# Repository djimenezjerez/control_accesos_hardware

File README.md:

# Hardware para el sistema de control de accesos

## Requisitos

Para abrir los archivos necesita tener instalado el software [KiCad](http://kicad-pcb.org/), con lo que podrá ejecutar los archivos .pro (Project) dentro de los cuales se encuentra el esquemático de la placa de interfaz sensorial que también cumple la función de control central de puertas, y la placa de respaldo bluetooth para apertura de puertas en caso de emergencia.

Para continuar el desarrollo de la aplicación de Android es necesario importar el archivo del proyecto [MIT App Inventor 2](./control_puertas.aia) y generar el APK desde la propia aplicación.

Los componentes del sistema son:

* [Hardware registrador](https://github.com/djimenezjerez/control_accesos_registrador)
* [Backend de administración del sistema](https://github.com/djimenezjerez/control_accesos_backend)
* [Frontend de administración del sistema](https://github.com/djimenezjerez/control_accesos_frontend)

## Documentación

* [LPG-Bolivia](https://softwarelibre.gob.bo/licencia.php)

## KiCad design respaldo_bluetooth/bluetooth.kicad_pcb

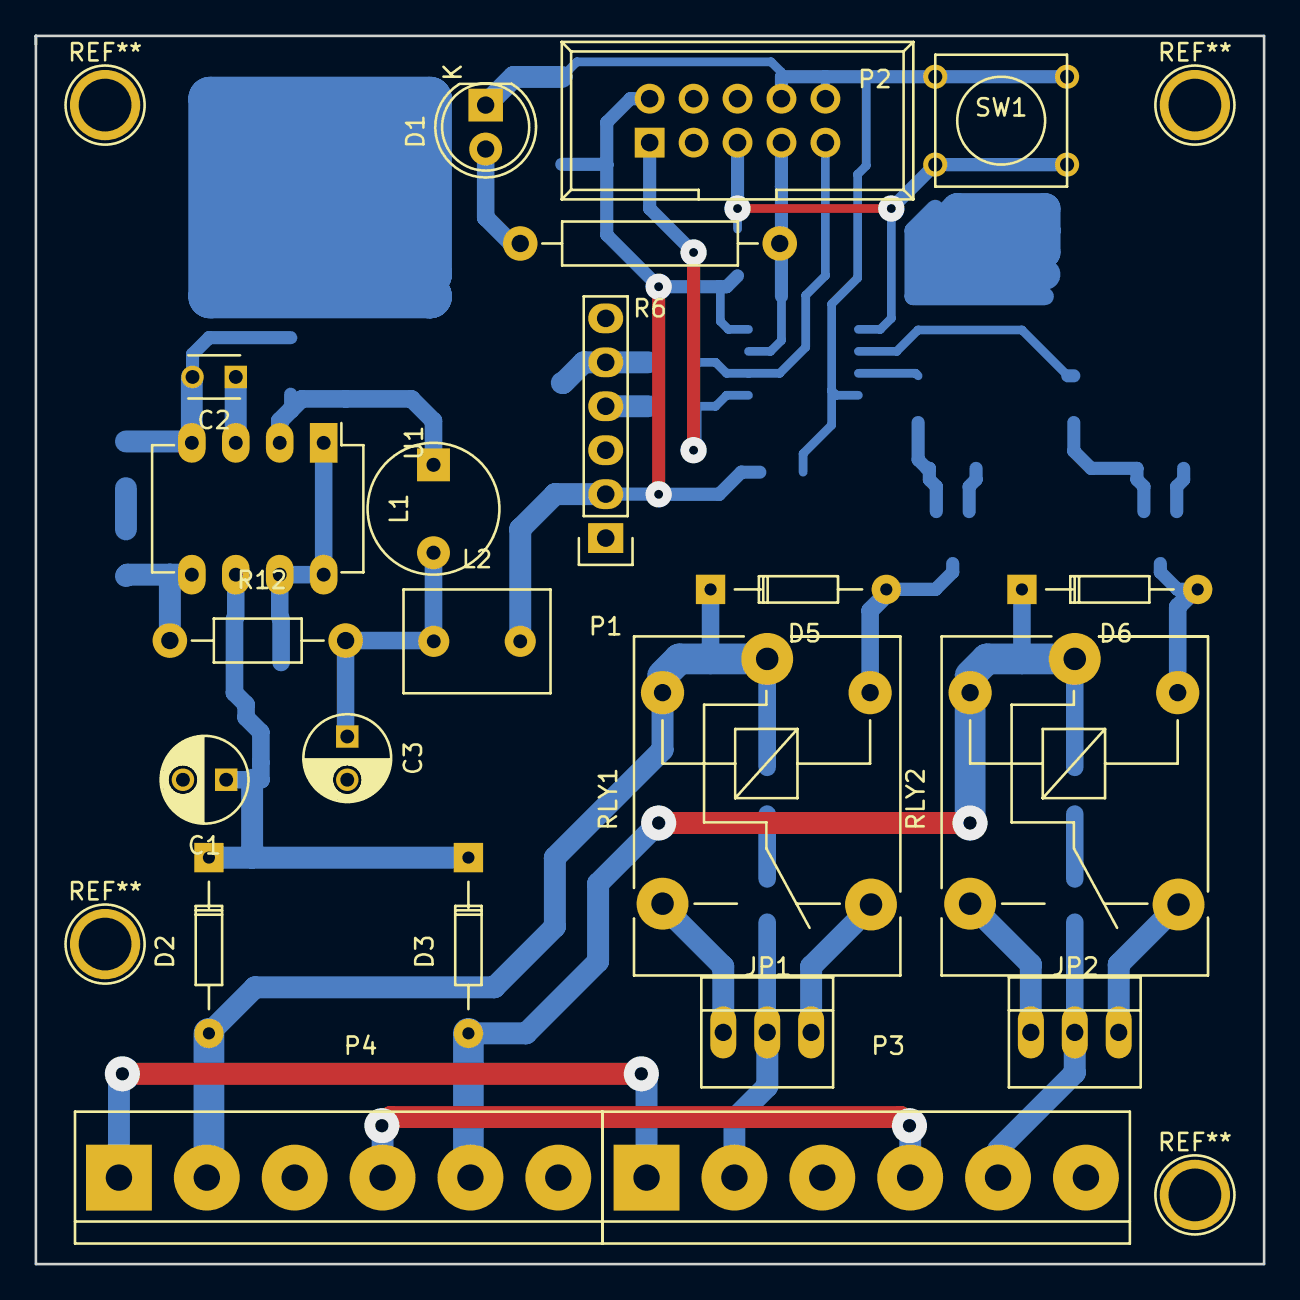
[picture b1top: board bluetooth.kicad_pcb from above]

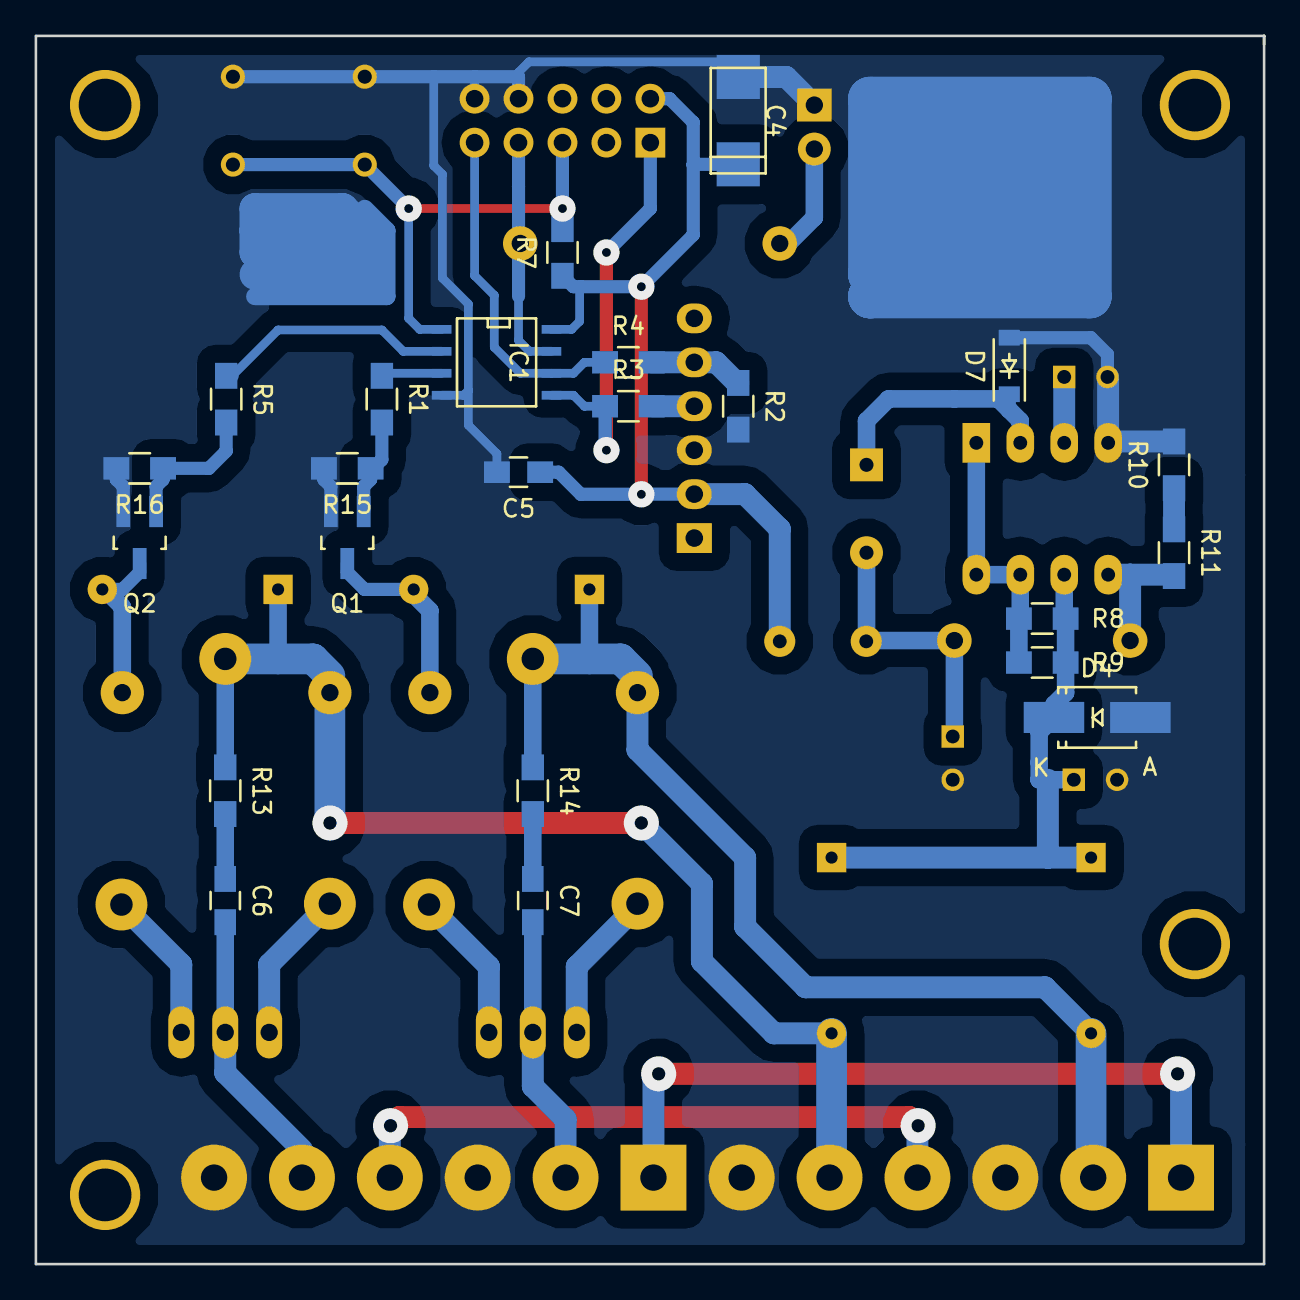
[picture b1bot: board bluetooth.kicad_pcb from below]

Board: 2 copper layers, 71.0 x 71.0 mm, 45 parts (23 on the bottom side), 34 nets.

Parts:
C1: 100uF; C_Radial_D5_L11_P2.5
C2: 470pF; C_Disc_D3_P2.5
C3: 47uF; C_Radial_D5_L11_P2.5
C4: 100uF; TantalC_SizeU_EIA-6032
C5, C6, C7: 100nF; C_0805_HandSoldering
D1: LED; LED-5MM
D2, D3: 1N4001; Diode_DO-35_SOD27_Horizontal_RM10
D4: TVS; SMA_Handsoldering
D5, D6: 1N4148; Diode_DO-35_SOD27_Horizontal_RM10
D7: 1N5819; SOD-123
IC1: ATTINY85-S; SOIC-8-N
JP1, JP2: NO/NC; PINHEAD1-3
L1: 150uH; INDUCTOR_V
L2: 150uH; Neosid_Inductor_MA-Bs75
P1: HC05-module; Pin_Header_Straight_1x06
P2: CONN_02X05; IDC_Header_Straight_10pins
P3: SALIDA; bornier6
P4: ENTRADA; bornier6
Q1, Q2: BCX70K; SOT-23_Handsoldering
R1, R2, R3, R4, R5, R7, R15, R16: R; R_0805_HandSoldering
R6: R; Resistor_Horizontal_RM15mm
R8, R9: 1R; R_0805_HandSoldering
R10: 1K; R_0805_HandSoldering
R11, R13, R14: 100R; R_0805_HandSoldering
R12: 3K3; Resistor_Horizontal_RM10mm
RLY1, RLY2: RELAY_HJR-3FF_Z; Relay_SANYOU_SRD_Series_Form_C
SW1: SW_PUSH; SW_PUSH_SMALL
U1: MC34063A; DIP-8_W7.62mm_LongPads

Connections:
+5V: C4.1, C5.1, IC1.8, L2.2, P1.2, P2.2, R7.1
GND: C1.2, C2.2, C3.2, C4.2, C5.2, D1.1, D4.2, D7.2, IC1.4, P1.3, P2.8, P2.10, P3.3, P3.6, P4.3, P4.6, Q1.2, Q2.2, R2.2, R10.2, R15.2, R16.2, SW1.1, U1.4
unnamed: C1.1, D2.1, D3.1, D4.1, R8.2, R9.2, U1.6
unnamed: C2.1, U1.3
unnamed: C3.1, L1.2, L2.1, R12.2
unnamed: C6.1, R13.2
unnamed: C6.2, JP2.2, P3.5
unnamed: C7.1, R14.2
unnamed: C7.2, JP1.2, P3.2
unnamed: D1.2, R6.2
unnamed: D2.2, D5.1, P4.2, R14.1, RLY1.1, RLY1.2
unnamed: D3.2, D6.1, P4.5, R13.1, RLY2.1, RLY2.2
unnamed: D5.2, Q1.3, RLY1.5
unnamed: D6.2, Q2.3, RLY2.5
unnamed: D7.1, L1.1, U1.2
unnamed: IC1.1, P2.5, R7.2, SW1.2
unnamed: IC1.2, R5.1
unnamed: IC1.3, R1.1
unnamed: IC1.5, P2.1, R3.1
unnamed: IC1.6, P2.9, R4.1
unnamed: IC1.7, P2.7, R6.1
unnamed: JP1.1, RLY1.3
unnamed: JP1.3, RLY1.4
unnamed: JP2.1, RLY2.3
unnamed: JP2.3, RLY2.4
unnamed: P1.4, R3.2
unnamed: P1.5, R2.1, R4.2
unnamed: P3.1, P4.1
unnamed: P3.4, P4.4
unnamed: Q1.1, R1.2, R15.1
unnamed: Q2.1, R5.2, R16.1
unnamed: R8.1, R9.1, U1.1, U1.7, U1.8
unnamed: R10.1, R11.1
unnamed: R11.2, R12.1, U1.5

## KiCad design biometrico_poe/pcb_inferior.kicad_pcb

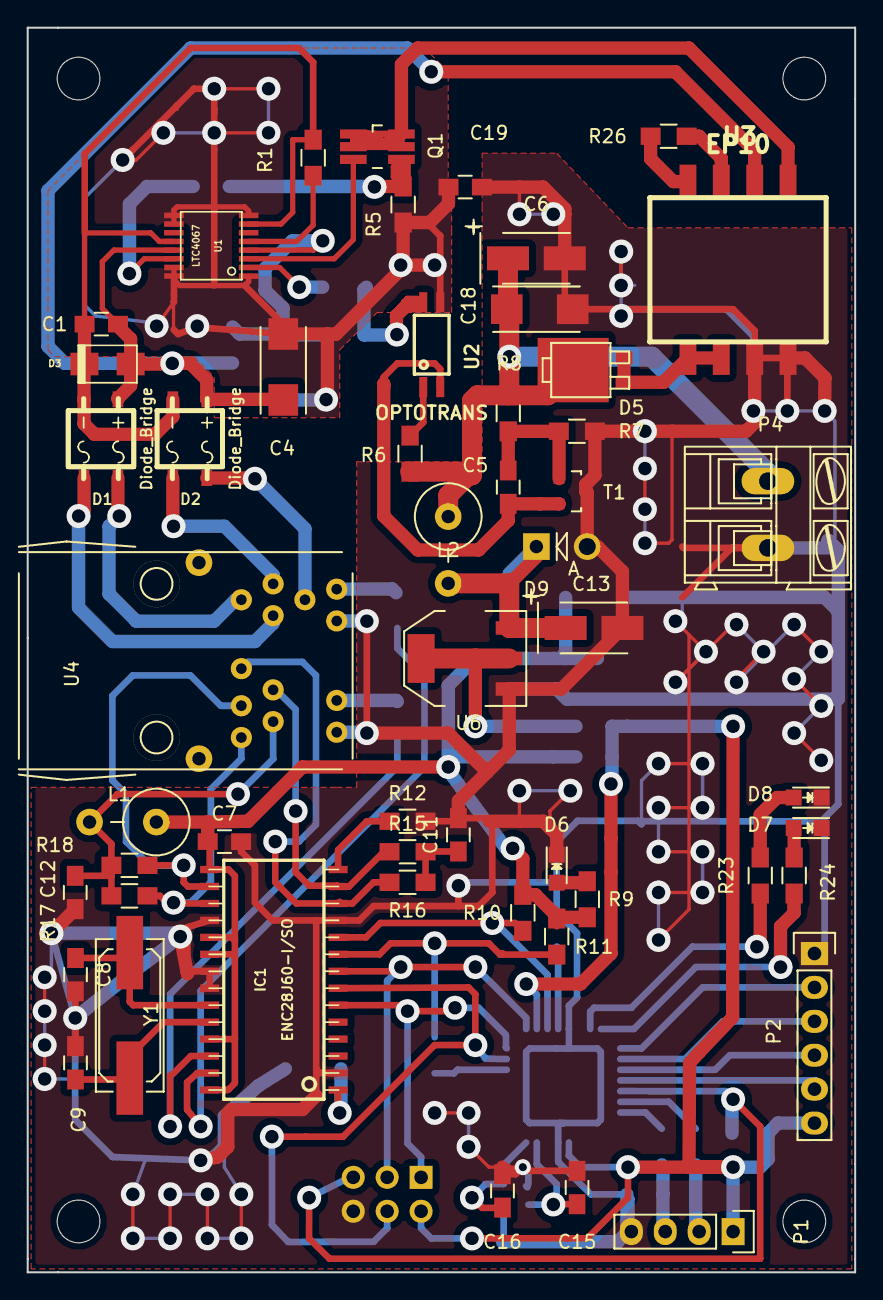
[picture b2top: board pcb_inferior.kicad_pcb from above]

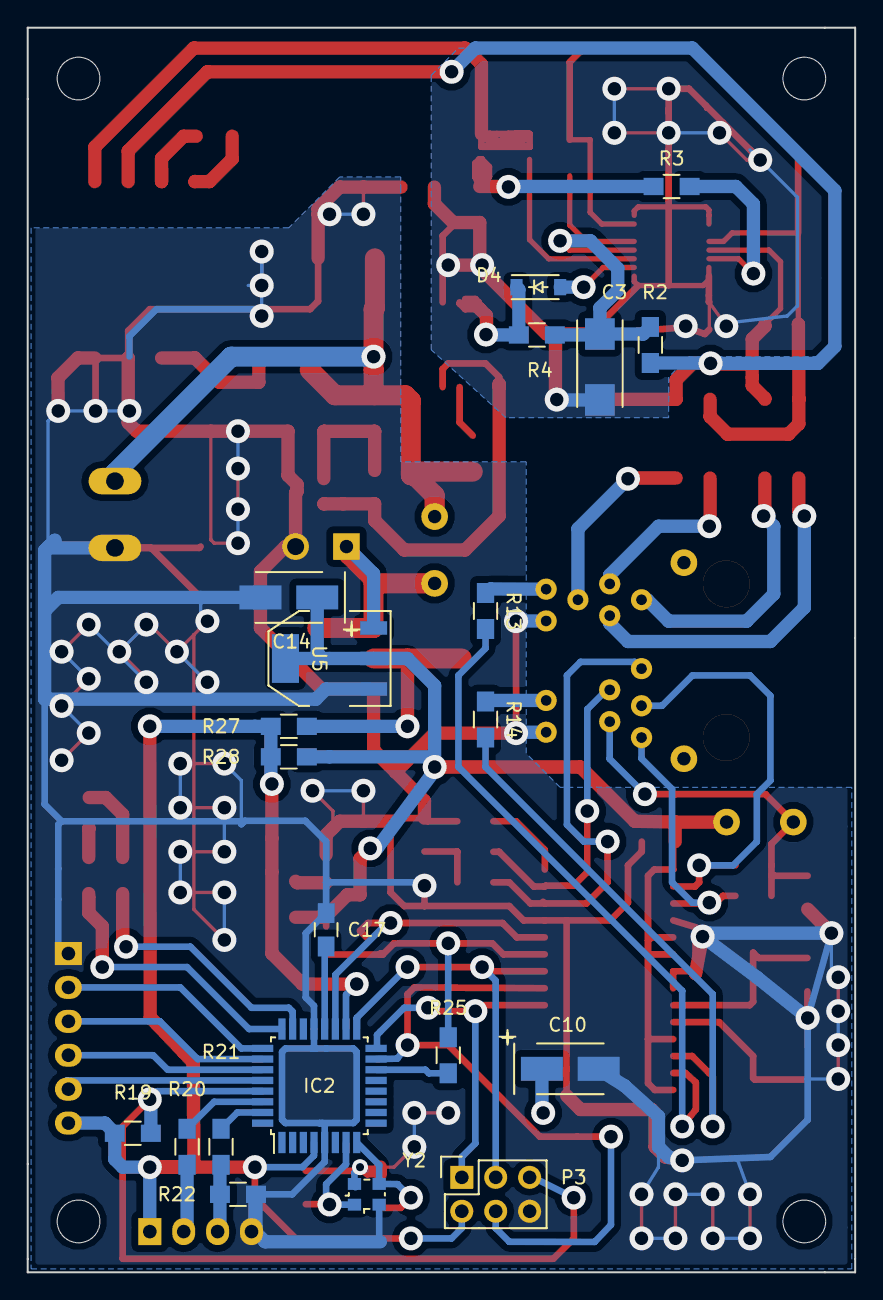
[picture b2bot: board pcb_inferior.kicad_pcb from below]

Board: 2 copper layers, 62.0 x 93.2 mm, 73 parts (21 on the bottom side), 64 nets.

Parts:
C1: CP1_Small; C_0805_HandSoldering
C3, C4: CP; TantalC_SizeC_EIA-6032_Reflow
C5, C7, C8, C9, C11, C12, C15, C16, C17, C19: C; C_0805_HandSoldering
C6: C; TantalC_SizeB_EIA-3528_HandSoldering
C10, C13, C14: CP; TantalC_SizeB_EIA-3528_HandSoldering
C18: CP1; TantalC_SizeC_EIA-6032_Reflow
D1, D2: Diode_Bridge; MBS
D3: ZENER; do214ac
D4: D; SOD-123
D5: D_Schottky; powermite3
D6, D7, D8: LED; LED_0805
D9: ZENER; Diode_DO-41_SOD81_Vertical_AnodeUp
IC1: ENC28J60-I/SO; soic-28
IC2: ATMEGA328P-A; TQFP-32_7x7mm_Pitch0.8mm
L1: L_Small; Resistor_Vertical_RM5mm
L2: INDUCTOR; Resistor_Vertical_RM5mm
P1: CONN_01X04; Pin_Header_Straight_1x04
P2: CONN_01X06; Socket_Strip_Straight_1x06
P3: CONN_02X03; Socket_Strip_Straight_2x03
P4: CONN_01X02; AK300-2
Q1: MOSFET_2512; TSOT-6-MK06A_Handsoldering
R1, R2, R3, R4, R5, R6, R7, R8, R9, R10, R11, R12, R13, R14, R15, R16, R17, R18, R19, R20, R21, R22, R23, R24, R25, R26, R27, R28: R; R_0805_HandSoldering
T1: SHUNT_REGULATOR; SOT-23
U1: LTC4067; tssop-16
U2: OPTOTRANS; mfp_4
U3: EP10; transf_smd_ep10-8
U4: MagJack_SI_52003; MG_SI_52003
U5, U6: AP1117; SOT-223
Y1: Crystal; Q_49U3HMS
Y2: Crystal_Small; Crystal_SMD_2520_4Pads

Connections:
/5V: IC2.4, IC2.18, P1.1, P2.6, P3.2, R19.1, R27.1, R28.2
/CS: IC2.14, R25.2
/CT: C12.1, L1.2, R17.2, R18.1, U4.2
/LED1: R13.1, U4.12
/LED2: R14.1, U4.14
/PVCC: C3.1, R2.2, R4.1, U1.4
/RD+: IC1.13, R15.1, U4.4
/RD-: IC1.12, R16.2, U4.5
/RST: IC1.10, IC2.19, R10.1
/RX: IC2.30, R20.2
/SCK: IC1.8, IC2.17, P3.3
/SI: IC1.7, IC2.15, P3.4
/SO: IC1.6, IC2.16, P3.1
/TD+: IC1.17, R17.1, U4.1
/TD-: IC1.16, R18.2, U4.3
/TX: IC2.31, R21.2
/VOUT: C6.1, C18.1, D5.2, L2.1, P4.1, R6.2, R8.1
GND: C3.2, C4.2, C19.2, R5.2, U1.1, U1.8, U1.9, U1.10, U1.15, U1.16, U2.3
GNDD: C6.2, C7.2, C8.2, C9.2, C10.2, C11.2, C12.2, C13.2, C14.2, C15.1, C16.1, C17.2, C18.2, C19.1, D6.1, D7.1, D8.1, D9.2, IC1.2, IC1.11, IC1.18, IC1.21, IC1.22, IC2.5, IC2.21, P1.4, P2.1, P3.6, P4.2, R7.2, R12.2, R22.2, T1.3, U3.5, U3.6, U4.13, U4.15, U5.1, U6.1
unnamed: C1.1, C4.1, D1.3, D2.3, D3.1, R2.1, U1.13, U3.3
unnamed: C1.2, D1.1, D2.1, D3.2, R1.2, U1.7, U1.12
unnamed: C5.1, T1.2, U2.2
unnamed: C5.2, R7.1, R8.2, T1.1
unnamed: C8.1, IC1.23, Y1.1
unnamed: C9.1, IC1.24, Y1.2
unnamed: C10.1, IC1.1
unnamed: C11.1, R15.2, R16.1
unnamed: C13.1, D9.1, L2.2, U5.3, U6.3
unnamed: C15.2, IC2.7, Y2.1
unnamed: C16.2, IC2.8, Y2.2
unnamed: C17.1, IC2.20
unnamed: D1.2, U4.8
unnamed: D1.4, U4.9
unnamed: D2.2, U4.10
unnamed: D2.4, U4.11
unnamed: D4.1, R4.2, U2.4
unnamed: D4.2, U1.2
unnamed: D5.1, U3.7, U3.8
unnamed: D6.2, R9.2
unnamed: D7.2, R24.1
unnamed: D8.2, R23.1
unnamed: IC1.9, R11.1, R25.1
unnamed: IC1.14, R12.1
unnamed: IC1.26, R14.2
unnamed: IC1.27, R13.2
unnamed: IC2.23, R23.2
unnamed: IC2.24, R24.2
unnamed: IC2.25, P2.2
unnamed: IC2.26, P2.3
unnamed: IC2.27, P2.4
unnamed: IC2.28, P2.5
unnamed: IC2.29, P3.5, R19.2
unnamed: P1.2, R20.1
unnamed: P1.3, R21.1, R22.1
unnamed: Q1.1, Q1.2, Q1.5, Q1.6, U3.4
unnamed: Q1.3, U1.3
unnamed: Q1.4, R3.1, R5.1
unnamed: R1.1, U1.5
unnamed: R3.2, U1.14
unnamed: R6.1, U2.1
unnamed: R26.1, U3.1
unnamed: R26.2, U3.2
unnamed: R27.2, U6.2
VCC: C7.1, C14.1, IC1.15, IC1.19, IC1.20, IC1.25, IC1.28, L1.1, R9.1, R10.2, R11.2, R28.1, U5.2

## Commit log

2017-07-18 Primera versión
2017-07-18 Añadida aplicación android
